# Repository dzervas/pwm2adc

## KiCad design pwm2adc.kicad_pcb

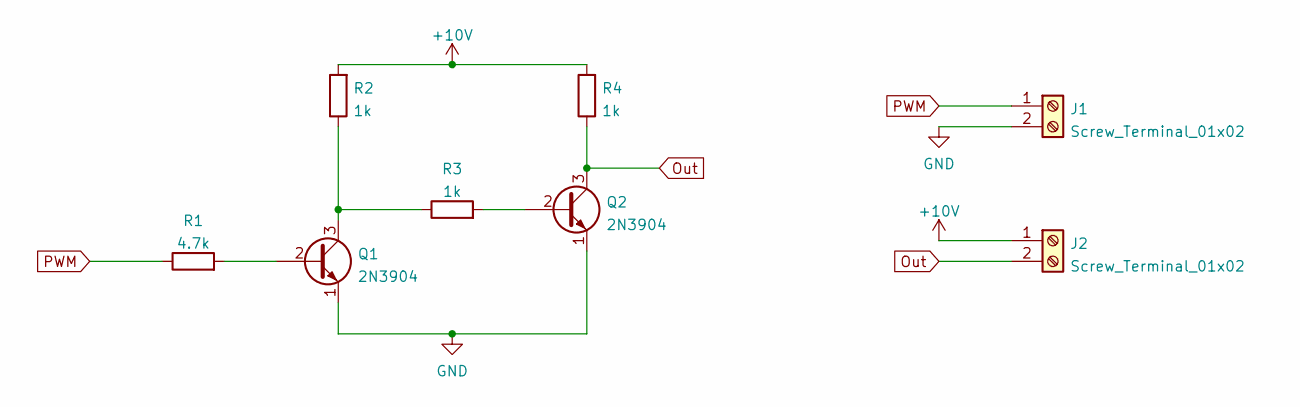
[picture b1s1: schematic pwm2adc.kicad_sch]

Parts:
J1, J2: Screw_Terminal_01x02; TerminalBlock_4Ucon_1x02_P3.50mm_Vertical
Q1, Q2: 2N3904; TO-92_Inline
R1: 4.7k; R_Axial_DIN0207_L6.3mm_D2.5mm_P10.16mm_Horizontal
R2, R3, R4: 1k; R_Axial_DIN0207_L6.3mm_D2.5mm_P10.16mm_Horizontal

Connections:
+10V: J2.1, R2.2, R4.2
GND: J1.2, Q1.1 (E), Q2.1 (E)
unnamed: Q1.2 (B), R1.2
unnamed: Q1.3 (C), R2.1, R3.1
unnamed: Q2.2 (B), R3.2
Out: J2.2, Q2.3 (C), R4.1
PWM: J1.1, R1.1

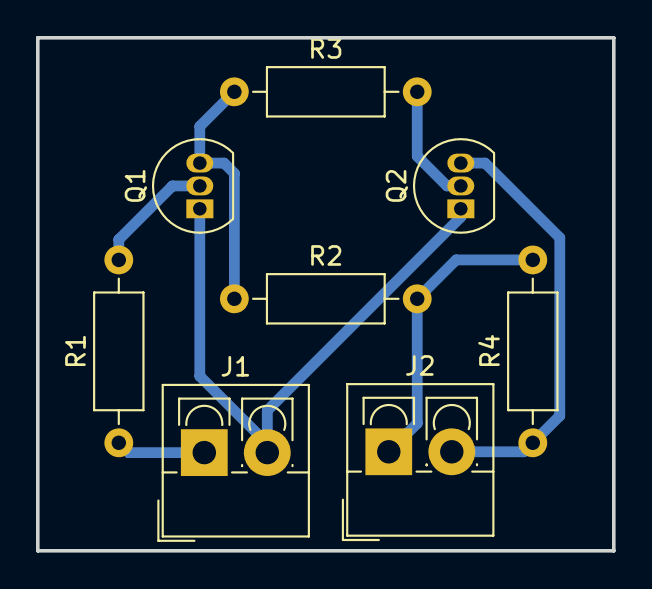
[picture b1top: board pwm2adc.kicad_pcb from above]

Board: 2 copper layers, 32.0 x 28.5 mm, 8 parts (0 on the bottom side), 7 nets.
